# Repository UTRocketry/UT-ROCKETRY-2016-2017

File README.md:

# UT Rocketry Active Control Unit #
## About ##
The Active Roll Control Unit (ARCU) is an electronics platform specially designed for the 2016-2017 NASA
University Student Launch Initiative (NASA USLI) by the University of Toledo Rocketry Club.

The ARCU accomplishes the task of controlling the roll orientation of a high powered rocket (HPR) after 
motor burnout. For the 2016-2017 USLI, NASA sets the requirement that the HPR must complete 2 rolls either
CW or CCW post motor burnout and hold the final roll orientation for the remainder of the flight. This is 
accomplished through the use of a servo motor that will control the angle of fins. The ARCU is composed of 
numerous components but most notably: ATmega32u4 microcontroller (MCU) now using the ESP8266 12E module, 
MPU9250 inertial measurement unit (IMU), and a micro SD card.

The ARCU is Arduino compatable and initially used the Sparkfun Pro Micro 3.3V 8MHz bootloader. Currently the 
system uses the ESP8266 ESP12E module. The MPU9250 is a magnetometer, accelerometer, and gyroscope chip that 
will be used for position feedback in the control loop. The library for the MPU9250 is available from Sparkfun. 
Gyro and Accelerometer data is used during the flight of the rocket to control the rocket. All data from the IMU
is logged during flight and magnetometer data is analyzed post flight to verify the roll of the rocket.

The final form of the ARCU is implemented as a custom printed circuit board (PCB). However since the ARCU 
uses parts available from Sparkfun, the ARCU can be assembled easily from off the shelf components either 
on a breadboard or using protyping board.Released versions of the ARCU PCB, ARCU ICSP tool, and the Backup
Breakout version are available in the "RELEASE" sub folder.

The University of Toledo Rocketry Club learned most of the information appparent in the design and construction 
of the ARCU through the internet. If it wasn't for websites like Adafruit or Sparkfun, the ARCU project would 
not be able to be completed. Knowing this, the University of Toledo Rocketry Club has made all designs of the 
ARCU available online for public access so that others can learn from the project. The ARCU is licensed under 
the GPL 3.0 license and is Open Source Hardware and Software.

## Revision History ##
### ATMega32U4 REV A ###
- This version had issues with USB connectivity and flashing the bootloader

### ATMega32U4 REV B ###
- This version attempted fix issues with the USB in the previous version, however the fixes were unsuccessful
- THe issues may have been due to the flashing tool that was used for the bootloader

### ESP8266 REV A ###
- This board was mostly functional with the exception of the interrupt pin on the 4 pin header being non-functional

### ICSP Tool ###

- This was designed to flash the bootloader on the boards running the ATMega32U4. Pinouts for the ICSP header are wrong and backwards
- This tool is printed at the same thickness as a standard micro SD card and is designed to fit into a micro SD card slot.

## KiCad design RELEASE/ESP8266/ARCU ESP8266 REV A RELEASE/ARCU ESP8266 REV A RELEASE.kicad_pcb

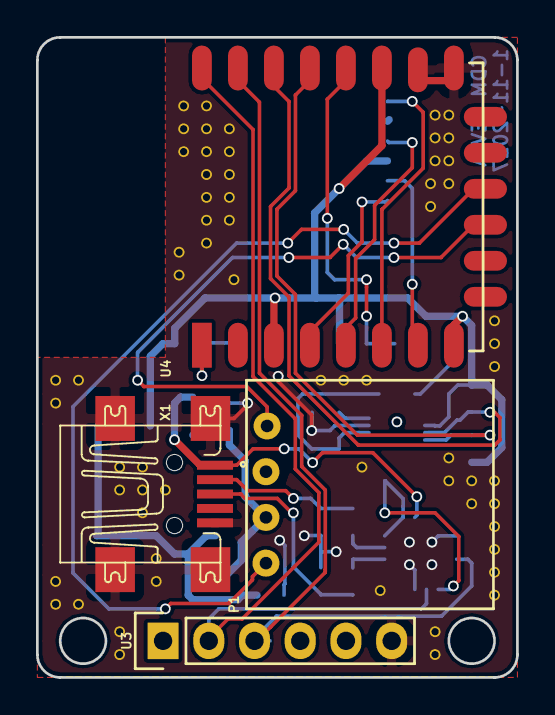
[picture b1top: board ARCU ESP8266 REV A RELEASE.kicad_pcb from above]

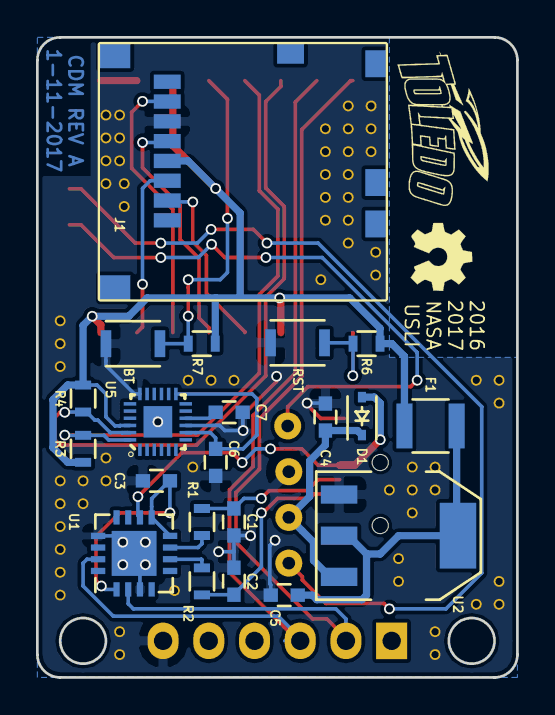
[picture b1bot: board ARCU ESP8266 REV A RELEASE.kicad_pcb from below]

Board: 2 copper layers, 26.7 x 35.6 mm, 25 parts (21 on the bottom side), 24 nets.

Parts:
BT: Push_SW; KXT 131 LHS
C1, C2: 47pF; C_0603
C3, C6, C7: .1uF; C_0603
C4: 10uF; C_0603
C5: 22uF; C_0603
D1: D_Schottky; SOD-323
F1: FUSE; R_1210
J1: 502570-0893; MOLEX_502570-0893
P1: TE1X4
R1, R2: 27; R_0603
R3, R4, R6, R7: 10K; R_0603
RST: Push_SW; KXT 131 LHS
U1: FT230XQ-R; QFN-16-1EP_4x4mm_Pitch0.65mm
U2: AZ1117; SOT-223
U3: FTDI; Pin_Header_Straight_1x06
U4: ESP-12E
U5: MPU-9250; QFN40P300X300X105-25N
X1: UX60-MB-5ST

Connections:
+3V3: F1.1, J1.4, R3.1, R4.1, R6.1, R7.1, U4.3, U4.8, U4.17, U5.22
+5V: D1.2, U1.10, X1.1
+9V: C4.1, D1.1, P1.2, U2.3
AUX: P1.4, U4.11
GND: BT.1, C1.2, C2.2, C3.2, C4.2, C5.2, C6.2, C7.2, J1.6, P1.3, RST.1, U1.3, U1.13, U1.17, U2.1, U3.6, U4.15, U4.16, U5.9, U5.18, X1.5, X1.M1, X1.M2, X1.M3, X1.M4
MISO: J1.7, U4.6
MOSI: J1.3, U4.7
unnamed: BT.2, R7.2, U4.18
unnamed: C1.1, R1.2, X1.2
unnamed: C2.1, R2.1, X1.3
unnamed: C3.1, U1.1, U1.8, U1.9
unnamed: C5.1, F1.2, U2.2
unnamed: C6.1, U5.8, U5.13
unnamed: C7.1, U5.10
unnamed: R1.1, U1.7
unnamed: R2.2, U1.6
unnamed: R6.2, RST.2, U4.1
RX_FTDI: U1.2, U3.2, U4.22
SCK: J1.5, U4.5
SCL: R4.2, U4.20, U5.23
SDA: R3.2, U4.19, U5.24
SD_CS: J1.2, U4.4
SERVO_PWM: P1.1, U4.12
TX_FTDI: U1.15, U3.3, U4.21

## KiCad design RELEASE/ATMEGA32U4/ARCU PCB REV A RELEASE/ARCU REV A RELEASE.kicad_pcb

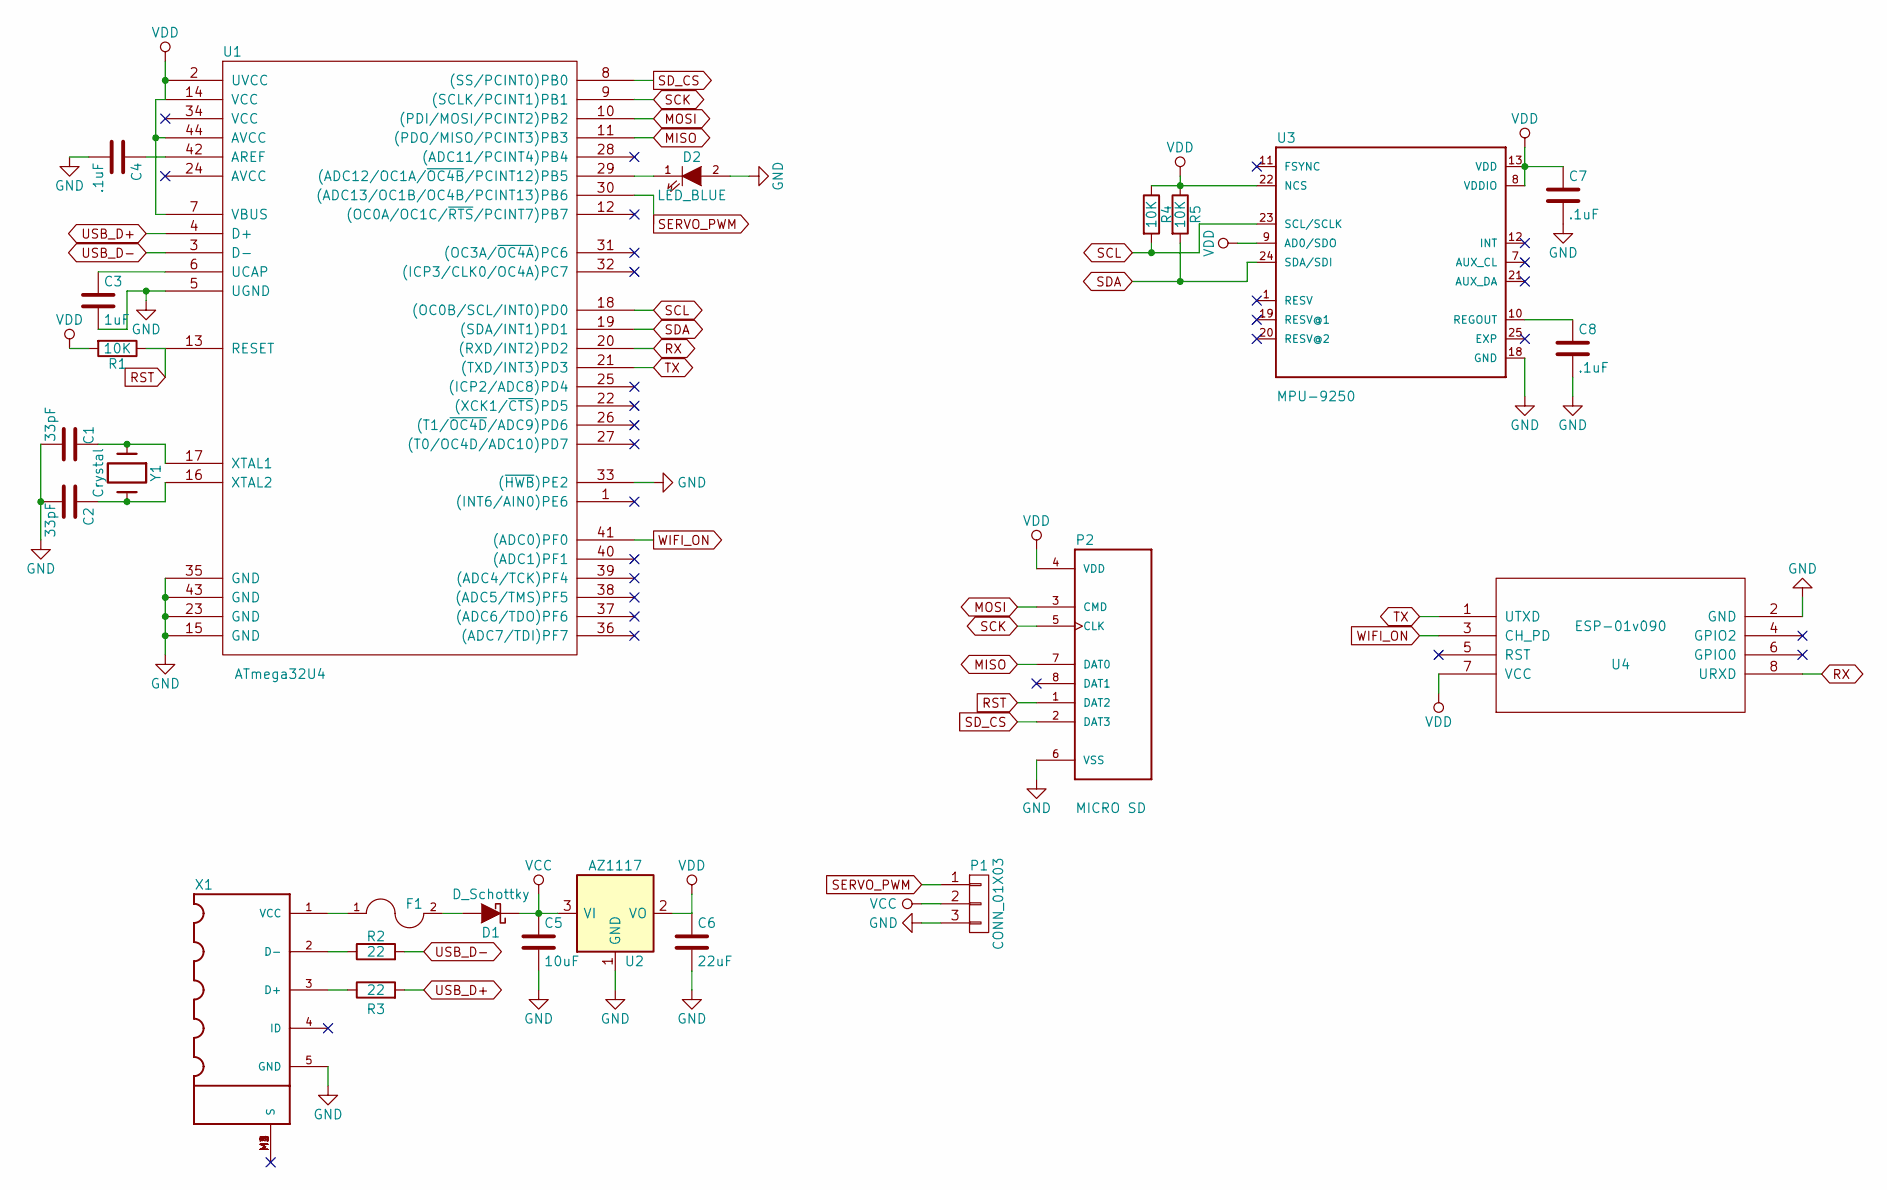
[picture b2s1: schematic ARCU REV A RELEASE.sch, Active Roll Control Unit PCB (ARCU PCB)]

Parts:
C1, C2: 33pF; C_0805
C3: 1uF; C_0805
C4, C7, C8: .1uF; C_0805
C5: 10uF; C_0805
C6: 22uF; C_0805
D1: D_Schottky; SOD-323
D2: LED_BLUE; LED_0805
F1: FUSE; R_1210
P1: CONN_01X03; TE1X3
P2: MICRO SD; HRS_DM3CS-SF
R1, R4, R5: 10K; R_0805
R2, R3: 22; R_0805
U1: ATmega32U4; TQFP-44_10x10mm_Pitch0.8mm
U2: AZ1117; SOT-223
U3: MPU-9250; QFN40P300X300X105-25N
U4: ESP-01v090; ESP-01
X1: SMD USB OTG; UX60-MB-5ST
Y1: Crystal; ABM3

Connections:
GND: C1.2, C2.2, C3.2, C4.2, C5.2, C6.2, C7.2, C8.2, D2.2 (A), P1.3, P2.6 (VSS), U1.5 (UGND), U1.15 (GND), U1.23 (GND), U1.33 ((~HWB~)PE2), U1.35 (GND), U1.43 (GND), U2.1 (GND), U3.18 (GND), U4.2 (GND), X1.5 (GND)
MISO: P2.7 (DAT0), U1.11 ((PDO/MISO/PCINT3)PB3)
MOSI: P2.3 (CMD), U1.10 ((PDI/MOSI/PCINT2)PB2)
unnamed: C1.1, U1.17 (XTAL1), Y1.1
unnamed: C2.1, U1.16 (XTAL2), Y1.2
unnamed: C3.1, U1.6 (UCAP)
unnamed: C4.1, U1.42 (AREF)
unnamed: C8.1, U3.10 (REGOUT)
unnamed: D1.2 (A), F1.2
unnamed: D2.1 (K), U1.29 ((ADC12/OC1A/~OC4B~/PCINT12)PB5)
unnamed: F1.1, X1.1 (VCC)
unnamed: R2.1, X1.2 (D-)
unnamed: R3.1, X1.3 (D+)
RST: P2.1 (DAT2), R1.1, U1.13 (RESET)
RX: U1.20 ((RXD/INT2)PD2), U4.8 (URXD)
SCK: P2.5 (CLK), U1.9 ((SCLK/PCINT1)PB1)
SCL: R4.2, U1.18 ((OC0B/SCL/INT0)PD0), U3.23 (SCL/SCLK)
SDA: R5.2, U1.19 ((SDA/INT1)PD1), U3.24 (SDA/SDI)
SD_CS: P2.2 (DAT3), U1.8 ((SS/PCINT0)PB0)
SERVO_PWM: P1.1, U1.30 ((ADC13/OC1B/OC4B/PCINT13)PB6)
TX: U1.21 ((TXD/INT3)PD3), U4.1 (UTXD)
USB_D+: R3.2, U1.4 (D+)
USB_D-: R2.2, U1.3 (D-)
VCC: C5.1, D1.1 (K), P1.2, U2.3 (VI)
VDD: C6.1, C7.1, P2.4 (VDD), R1.2, R4.1, R5.1, U1.2 (UVCC), U1.7 (VBUS), U1.14 (VCC), U1.44 (AVCC), U2.2 (VO), U3.8 (VDDIO), U3.9 (AD0/SDO), U3.13 (VDD), U3.22 (NCS), U4.7 (VCC)
WIFI_ON: U1.41 ((ADC0)PF0), U4.3 (CH_PD)

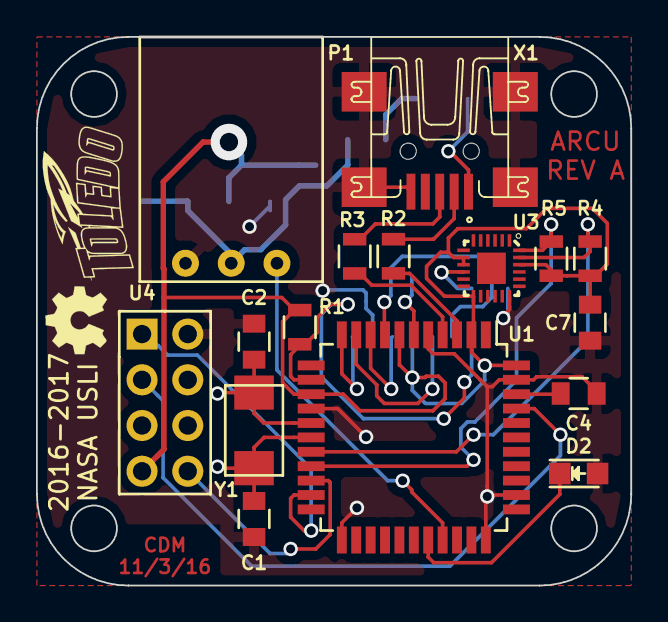
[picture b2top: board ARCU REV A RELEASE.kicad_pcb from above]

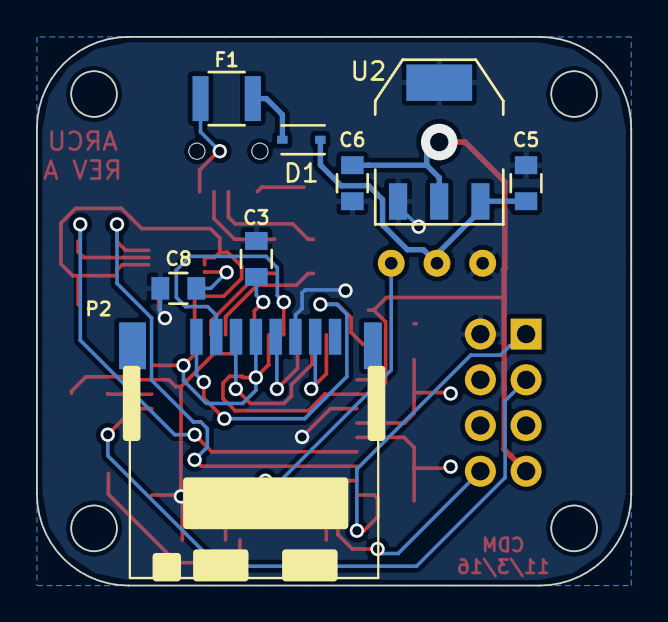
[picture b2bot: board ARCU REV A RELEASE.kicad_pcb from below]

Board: 2 copper layers, 33.0 x 30.5 mm, 24 parts (8 on the bottom side), 26 nets.

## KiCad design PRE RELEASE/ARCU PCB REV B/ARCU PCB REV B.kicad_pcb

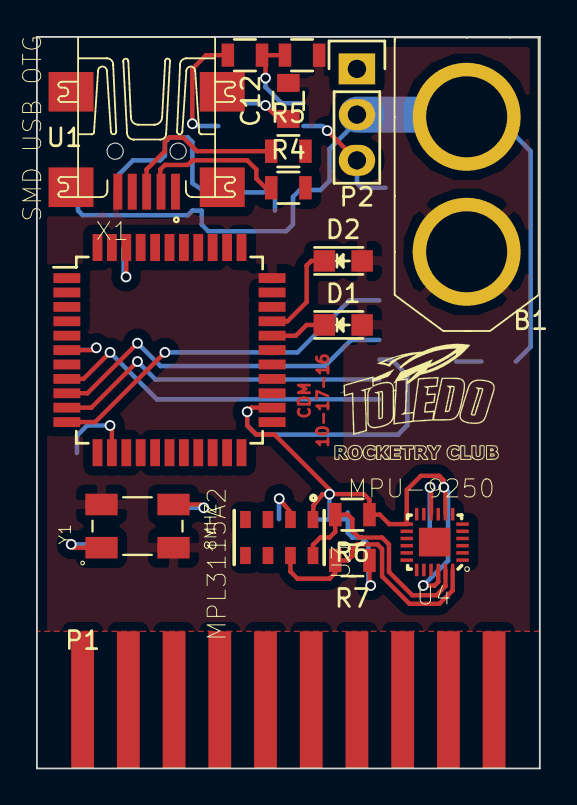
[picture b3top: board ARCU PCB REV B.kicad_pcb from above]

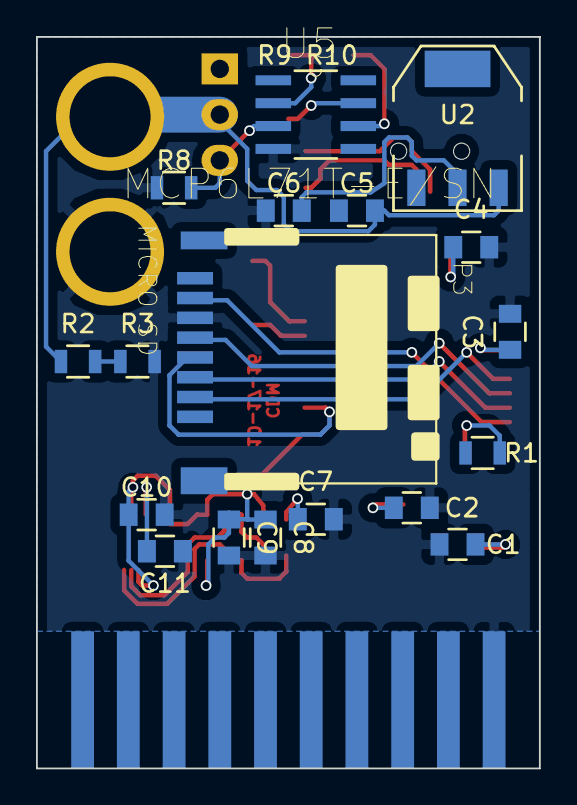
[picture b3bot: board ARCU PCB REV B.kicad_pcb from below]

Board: 2 copper layers, 27.9 x 40.6 mm, 35 parts (18 on the bottom side), 34 nets.

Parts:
B1: CONN_01X02; XT60
C1, C2: 33pF; C_0805
C3: 1uF; C_0805
C4, C7, C8, C10, C11, C12: .1uF; C_0805
C5, C9: 10uF; C_0805
C6: 22uF; C_0805
D1, D2: LED_BLUE; LED_0805
P1: CONN_02X10; Card Edge 2x10 B
P2: SERVO; Pin_Header_Straight_1x03
P3: MICRO SD; HRS_DM3CS-SF
R1, R6, R7: 10K; R_0805
R2: 3K; R_0805
R3: 1K; R_0805
R4, R5: 22; R_0805
R8: .01; R_0805
R9: 200; R_0805
R10: 13K; R_0805
U1: ATmega32U4; TQFP-44_10x10mm_Pitch0.8mm
U2: AZ1117; SOT-223
U3: MPL3115A2; PSON125P300X500X120-8N
U4: MPU-9250; QFN40P300X300X105-25N
U5: MCP6L71T-E/SN; SOIC127P600X175-8N
X1: SMD USB OTG; UX60-MB-5ST
Y1: 8MHZ; OSCSC500X320X110-4N

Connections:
E1: P1.11, U1.41
E2: P1.12, U1.40
E3: P1.13, U1.39
E4: P1.14, U1.38
GND: B1.2, C1.2, C2.2, C3.2, C4.2, C5.2, C6.2, C7.2, C8.2, C9.2, C10.2, C11.2, C12.2, D1.2, D2.2, P1.2, P3.6, R3.2, R8.2, R9.2, U1.5, U1.15, U1.23, U1.33, U1.35, U1.43, U2.1, U3.3, U4.9, U4.18, U5.4, X1.5, Y1.2, Y1.4
MCU_LED: D2.1, U1.30
MISO: P1.3, P3.7, U1.11
MOSI: P1.6, P3.3, U1.10
unnamed: C1.1, U1.17, Y1.1
unnamed: C2.1, U1.16, Y1.3
unnamed: C3.1, U1.6
unnamed: C4.1, U1.42
unnamed: C7.1, U3.2
unnamed: C11.1, U4.10
unnamed: R4.1, X1.2
unnamed: R5.1, X1.3
unnamed: R9.1, R10.2, U5.2
unnamed: X1.M1, X1.M2, X1.M3, X1.M4
RST: P1.4, R1.1, U1.13
RX: P1.7, U1.20
SCK: P1.5, P3.5, U1.9
SCL: P1.10, R6.2, U1.18, U3.8, U4.23
SDA: P1.9, R7.2, U1.19, U3.7, U4.24
SD_CS: P3.2, U1.8
SERVO_PWM: P2.1, U1.28
SERVO_S_V: P2.3, R8.1, U5.3
SERVO_S_V_A: R10.1, U1.36, U5.6
TX: P1.8, U1.21
USB_D+: R5.2, U1.4
USB_D-: R4.2, U1.3
VCC: B1.1, C5.1, P2.2, R2.1, U2.3
VCC_V: R2.2, R3.1, U1.37
VCC_V_LED: D1.1, U1.29
VDD: C6.1, C8.1, C9.1, C10.1, C12.1, P1.1, P3.4, R1.2, R6.1, R7.1, U1.2, U1.7, U1.14, U1.24, U1.34, U1.44, U2.2, U3.1, U3.4, U4.8, U4.13, U4.22, U5.7

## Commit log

2016-11-06 Create ABOUT
2016-11-09 added BOM
2016-11-09 commented on location of released files
2016-11-15 Add files via upload
    Added gerber files
2016-12-31 Added REV B
2017-02-28 Split RELEASE into sub folders. Added MOD footprints
2018-01-01 readme
2018-01-01 new folders
2018-01-01 images
